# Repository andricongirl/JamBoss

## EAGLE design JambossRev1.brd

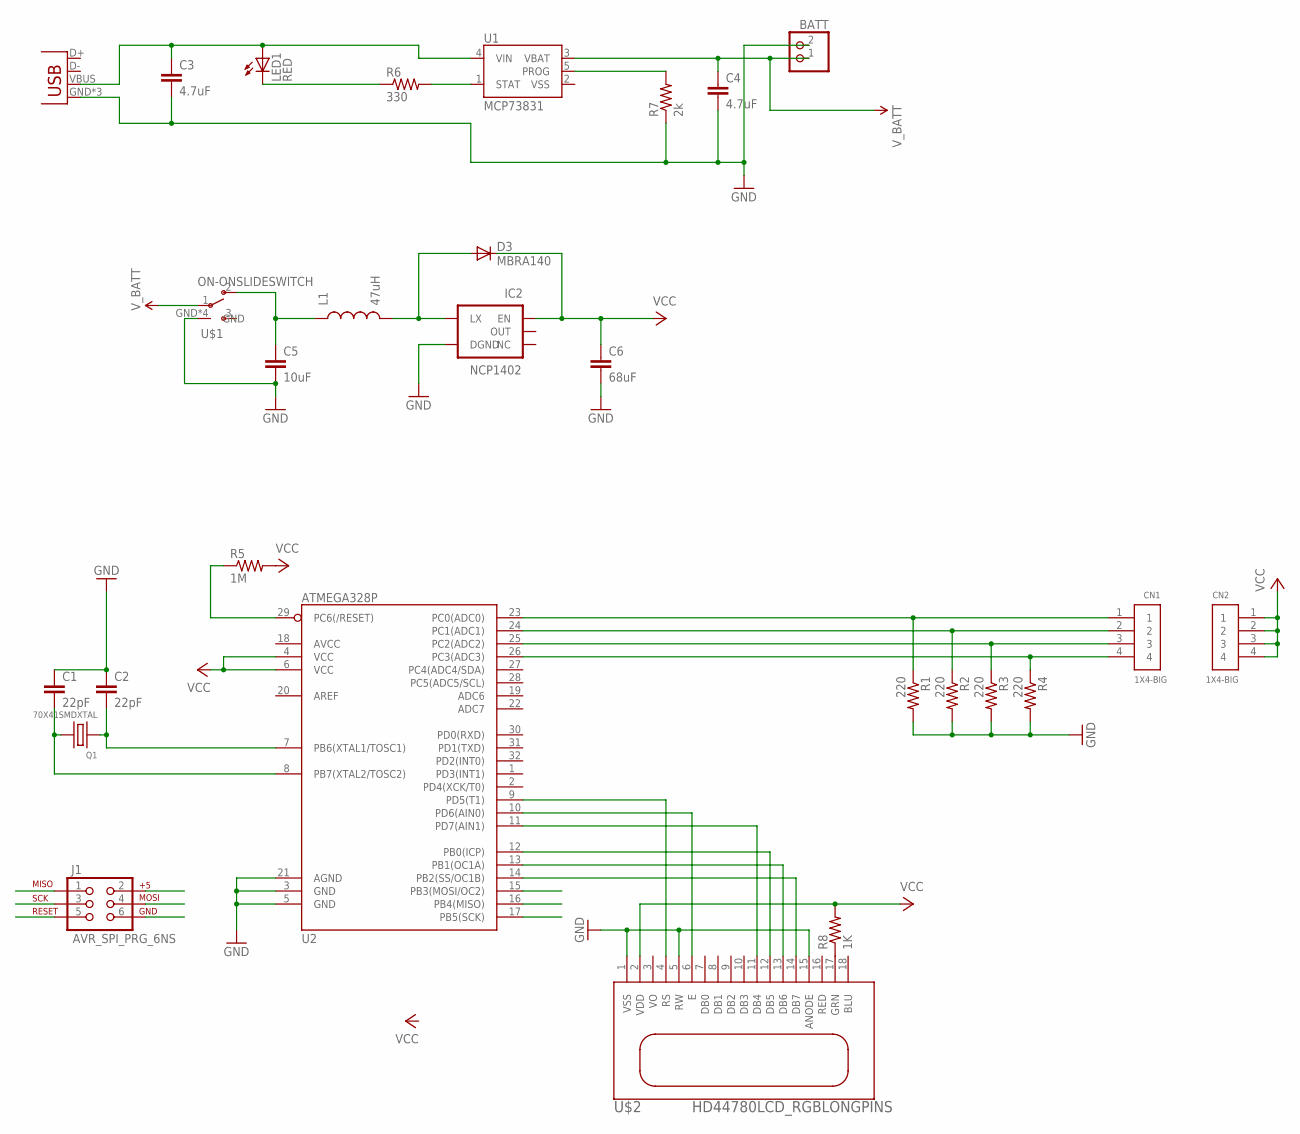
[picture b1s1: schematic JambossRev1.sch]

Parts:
BATT: JST_2PIN-THM-RA; JST-PH-2-THM-RA
C1, C2: 22pF; 0805
C3, C4: 4.7uF; 0603-CAP
C5: 10uF; 1206
C6: 68uF; 0805
CN1, CN2: 1X4-BIG; 1X04-BIG
D3: MBRA140; SMA-DIODE
IC2: NCP1402; SOT23-5
J1: AVR_SPI_PRG_6NS; 2X3-NS
JP1: USB-MICROB
L1: 47uH; 0805
LED1: RED; LED-0603
Q1: 70X41SMDXTAL; XTAL-70X41
R1, R2, R3, R4: 220; 0805
R5: 1M; R0603
R6: 330; 0603-RES
R7: 2k; 0603-RES
R8: 1K; 0805
U1: MCP73831; SOT23-5
U2: ATMEGA328P; TQFP32-08
U$1: ON-ONSLIDESWITCH; ONOFFSWITCHSMD
U$2: HD44780LCD_RGBLONGPINS; LCD1602-RGB

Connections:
GND: BATT.2 (1), C1.1, C2.1, C3.2, C4.2, C5.2, C6.2, IC2.4 (DGND), J1.6, JP1.GND (DGND), JP1.MT1 (DGND), JP1.MT2 (DGND), R1.2, R2.2, R3.2, R4.2, R7.1, U1.2 (VSS), U2.3 (GND), U2.5 (GND), U2.21 (AGND), U$1.GND, U$1.GND2 (GND), U$1.GND3 (GND), U$1.GND4 (GND), U$2.1 (VSS), U$2.5 (RW), U$2.15 (ANODE)
GRN: R8.1, U$2.17 (GRN)
MISO: J1.1, U2.16 (PB4(MISO))
MOSI: J1.4, U2.15 (PB3(MOSI/OC2))
unnamed: C2.2, Q1.P$1, U2.7 (PB6(XTAL1/TOSC1))
unnamed: C1.2, Q1.P$2, U2.8 (PB7(XTAL2/TOSC2))
unnamed: U2.14 (PB2(SS/OC1B)), U$2.14 (DB7)
unnamed: U2.13 (PB1(OC1A)), U$2.13 (DB6)
unnamed: U2.12 (PB0(ICP)), U$2.12 (DB5)
unnamed: U2.11 (PD7(AIN1)), U$2.11 (DB4)
unnamed: U2.10 (PD6(AIN0)), U$2.6 (E)
unnamed: LED1.C, R6.1
unnamed: CN1.2, R2.1, U2.24 (PC1(ADC1))
unnamed: CN1.1, R1.1, U2.23 (PC0(ADC0))
unnamed: U2.9 (PD5(T1)), U$2.4 (RS)
unnamed: CN1.3, R3.1, U2.25 (PC2(ADC2))
unnamed: CN1.4, R4.1, U2.26 (PC3(ADC3))
unnamed: R6.2, U1.1 (STAT)
unnamed: R7.2, U1.5 (PROG)
unnamed: C3.1, JP1.VBUS, LED1.A, U1.4 (VIN)
unnamed: D3.A, IC2.5 (LX), L1.2
unnamed: C5.1, L1.1, U$1.2
RESET: J1.5, R5.1, U2.29 (PC6(/RESET))
SCK: J1.3, U2.17 (PB5(SCK))
VCC: C6.1, CN2.1, CN2.2, CN2.3, CN2.4, D3.C, IC2.1 (EN), J1.2, R5.2, R8.2, U2.4 (VCC), U2.6 (VCC), U$2.2 (VDD)
V_BATT: BATT.1 (2), C4.1, U1.3 (VBAT), U$1.1

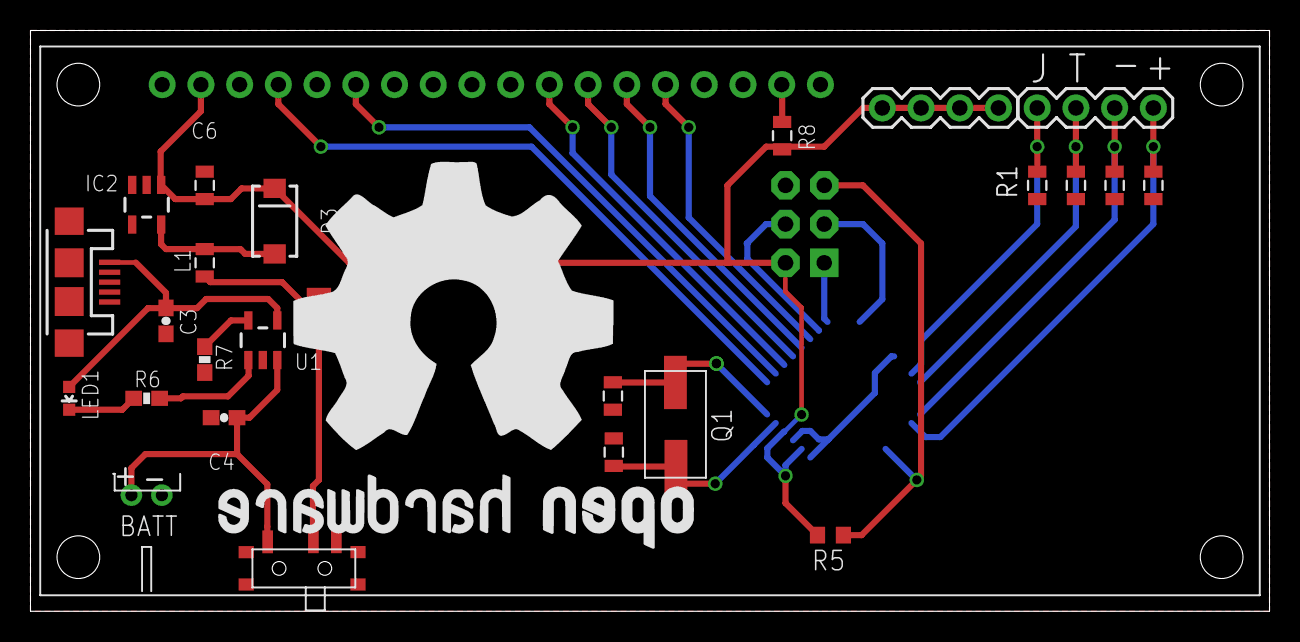
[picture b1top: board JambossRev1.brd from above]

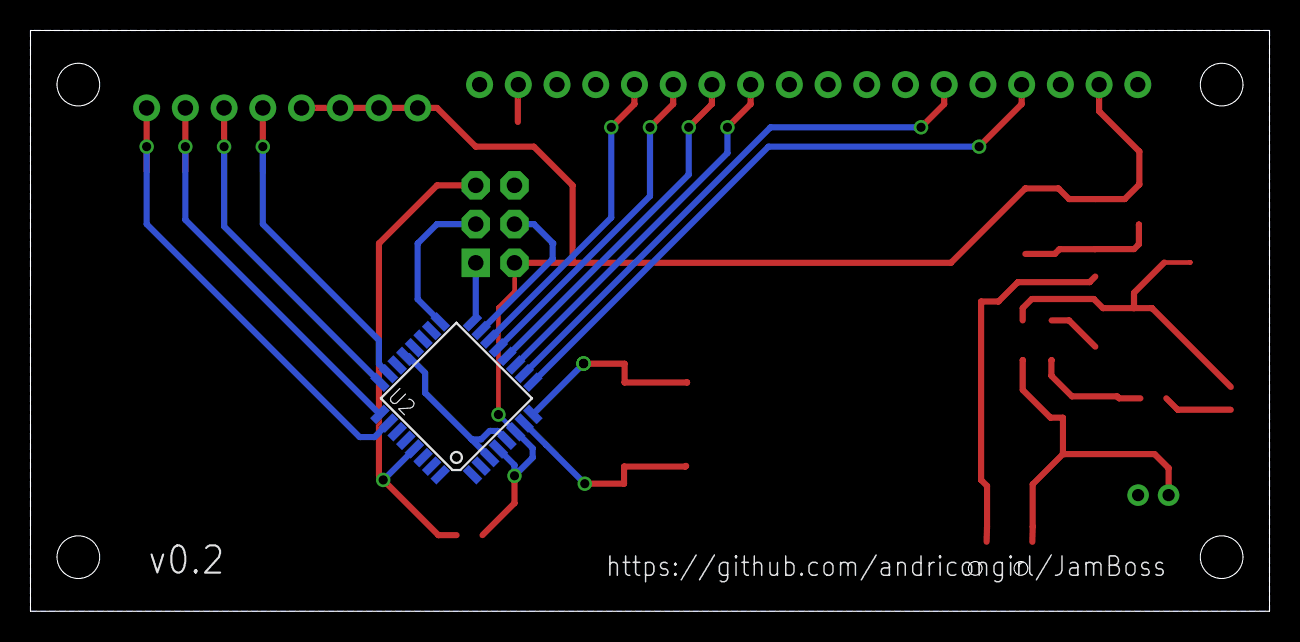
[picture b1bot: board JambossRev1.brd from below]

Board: 2 copper layers, 81.3 x 38.1 mm, 29 parts (2 on the bottom side), 26 nets.

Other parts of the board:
U$3: OSH-LOGO-HUGE

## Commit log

2013-10-19 Added Sketch Files
2013-10-19 Added Sketches
2013-10-19 Added EAGLE files to .gtignore
2013-10-21 Created a LCD Version
    As opposed to OLED which is more expensive. ~$15 vs $32
    Looking at Digikey NHD-0216K1Z-NSW-BBW-L-ND Or Digikey
    NHD-0216K1Z-NS(RGB)-FBW-REV1-ND component.
2013-10-27 Changed Pinout to accomodate ISP
2013-10-27 Added more temp files to gtignore
2014-02-05 0.2. Changed Micro and Misc Changes
    Added Copyright to Sketch, redid .brd layout with a TQFP-32.
2014-02-06 gitignore update for eagle files
2014-02-18 Board Layout
    Improved silk readability
    Moved the LCD resistor to the proper place
2014-02-18 Switch, silkscreen, xtal
    Fixed on/off switch connections
    Swapped xtal for identical with smaller footprint, shorter profile
    (saved 3 cents)
    Arranged silk labels for easier reading
    Added OSH logo and github URL to bottom silk

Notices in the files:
parts and their libraries:
SparkFun-PowerIC: Licensing: CC v3.0 Share-Alike You are welcome to use this library for commercial purposes.
